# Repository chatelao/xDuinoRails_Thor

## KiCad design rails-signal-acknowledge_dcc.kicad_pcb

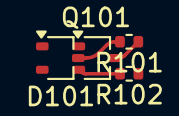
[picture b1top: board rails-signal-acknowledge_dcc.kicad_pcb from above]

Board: 2 copper layers, 4 parts (0 on the bottom side), 3 nets.

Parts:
D101: BAT54CW; SOT-323_SC-70
Q101: BSS138W; SOT-323_SC-70
R101: 100R; R_0402_1005Metric
R102: 10k; R_0402_1005Metric

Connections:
/DCC+: D101.3, R101.2
/DCC+_DROP: Q101.3 (C), R101.1
/DCC_ACK_IN: Q101.2 (B), R102.2

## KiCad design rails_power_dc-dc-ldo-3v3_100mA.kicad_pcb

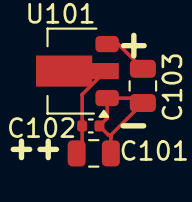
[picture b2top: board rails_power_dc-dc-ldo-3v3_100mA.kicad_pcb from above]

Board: 2 copper layers, 4 parts (0 on the bottom side), 3 nets.

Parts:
C101: 22uF; C_0805_2012Metric
C102: 1u; C_0402_1005Metric
C103: 47uF; C_0805_2012Metric
U101: HT75xx-1-SOT89; SOT-89-3

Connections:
/+3V3: C103.1, U101.3 (VOUT)
/GND: C101.2, C102.2, C103.2, U101.1 (GND)
/U+: C101.1, C102.1, U101.2 (VIN)
